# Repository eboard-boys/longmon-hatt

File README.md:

# longmon-hatt
Schematic and PCB for ESP32 HAT for the Longboard Wrist Monitor

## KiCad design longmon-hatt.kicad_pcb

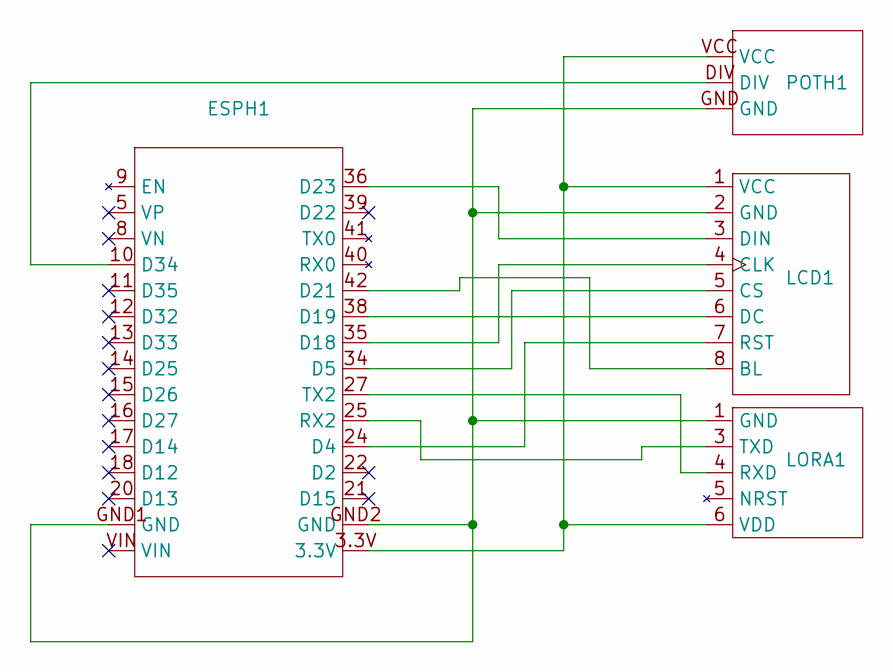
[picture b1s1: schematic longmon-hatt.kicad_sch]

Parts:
ESPH1: ESP_Header
LCD1: LCD Module
LORA1: LoRa Header
POTH1: POT Header

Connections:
unnamed: ESPH1.24 (D4), LCD1.7 (RST)
unnamed: ESPH1.34 (D5), LCD1.5 (CS)
unnamed: ESPH1.35 (D18), LCD1.4 (CLK)
unnamed: ESPH1.38 (D19), LCD1.6 (DC)
unnamed: ESPH1.42 (D21), LCD1.8 (BL)
unnamed: ESPH1.36 (D23), LCD1.3 (DIN)
unnamed: ESPH1.10 (D34), POTH1.DIV
unnamed: ESPH1.25 (RX2), LORA1.3 (TXD)
unnamed: ESPH1.27 (TX2), LORA1.4 (RXD)
unnamed: ESPH1.GND1 (GND), ESPH1.GND2 (GND), LCD1.2 (GND), LORA1.1 (GND), POTH1.GND
unnamed: ESPH1.3.3V, LCD1.1 (VCC), LORA1.6 (VDD), POTH1.VCC

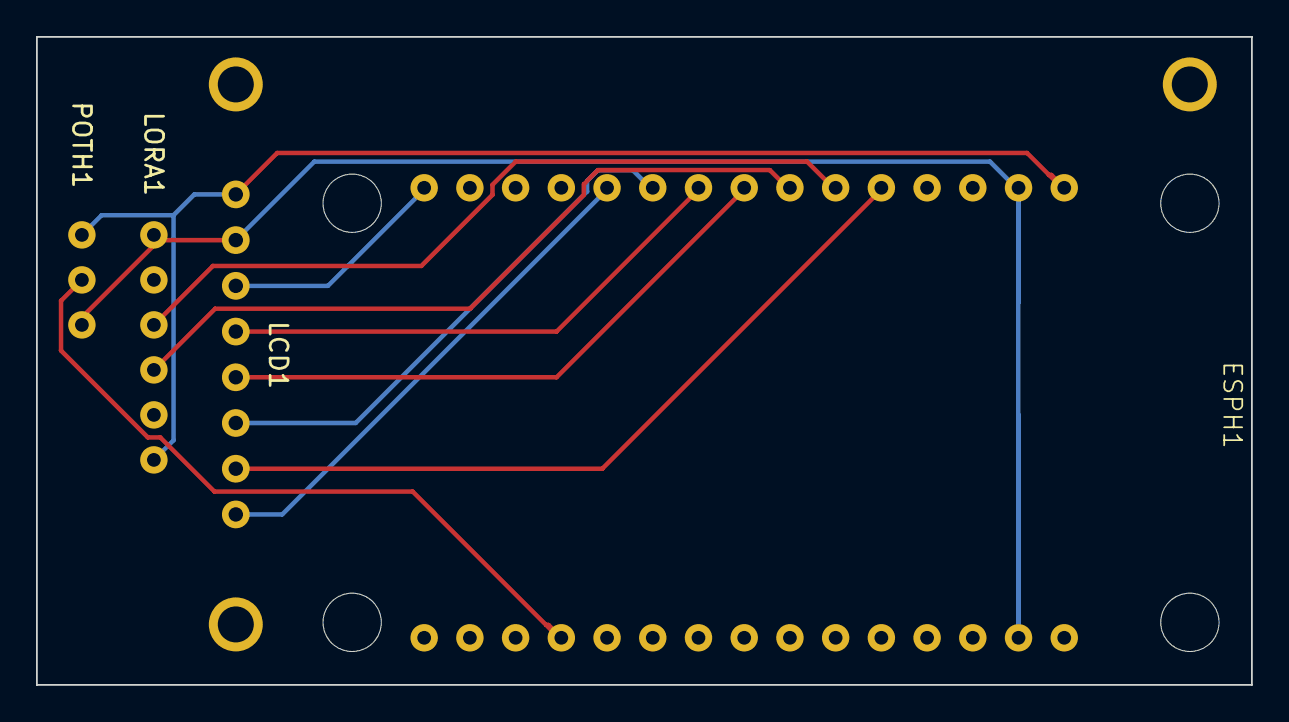
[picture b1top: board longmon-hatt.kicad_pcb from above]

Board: 2 copper layers, 67.5 x 36.0 mm, 4 parts (0 on the bottom side), 11 nets.

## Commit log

2023-10-31 Start making ESP32 Devkit Hat
2023-11-01 Add the symbols and footprints to the project to make them more portable
2023-11-01 Correctly position ESP mounting holes on footprint
2023-11-02 Add LCD Module footprint, update ESP schematic to point to new footprint
2023-11-02 Begin schematic
2023-11-02 Modify LoRa module to include additional pin (unused)
2023-11-05 Close to final schematic, starting PCB I suck at PCB design
2023-11-08 Ignore mutex files?
2023-11-08 Fixed pad numbers on ESP footprint, fix ref designators on PCB
2023-11-08 Add LoRa header (TODO: fix pin order), add edge cut
2023-11-08 Fix LoRa pins and pads, add design constraints
2023-11-08 Add POT header
2023-11-09 Fix pads and footprint on LCD
2023-11-09 Extend pcb 0.5mm down
2023-11-09 Fix LCD pin2 bug
2023-11-09 Add silkscreen constrains, smaller LCD pads
2023-11-09 Add LCD to PCB
2023-11-09 Remove LCD 4th mounting hole, silkscreen thickness to 0.153mm
2023-11-10 Autoroute traces
2023-11-10 Finalize PCB for ordering
2023-11-10 Fixed LCD pins not being connected bug
2023-11-10 Autorouted traces
2024-07-27 Added images and photos of PCB
2024-07-27 Add PCB top image to README.md
2024-07-27 Remove PCB Top, Add PCB Editor and Assembly images to README.md
2024-07-27 Rename pictures folder to images
2024-07-27 Change file path to new images folder in README.md
2025-02-05 Replace ESP32 with imported library
2025-08-08 Put hat in all caps README.md
